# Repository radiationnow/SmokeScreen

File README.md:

# SmokeScreen
SmokeScreen is a NodeMCU/ESP32-based smoker temperature monitor/controller using MQTT for communication.

(Well, it'll be a controller some day.  For now, just a monitor.)

Simple circuit: NodeMCU ESP32 board, 2x 15k resistors to form the bottom leg of voltage dividers, and a pair of panel mount 2.5mm TS (mono) jacks.  (Fritzing only had stereo, but use mono.) 

Probe coefficients are hand calibrated using a known-good instant read thermometer, an ice bath, a warm bath, and a boiling bath.  Probes tested with include Thermoworks High Temp Air, Thermoworks normal probe, and a clone ET-733 probe.  Pit thermistor voltage divider center measured on pin 32, meat thermistor on pin 33.

Loosely inspired by CapnBry's HeaterMeter - https://github.com/CapnBry/HeaterMeter/.

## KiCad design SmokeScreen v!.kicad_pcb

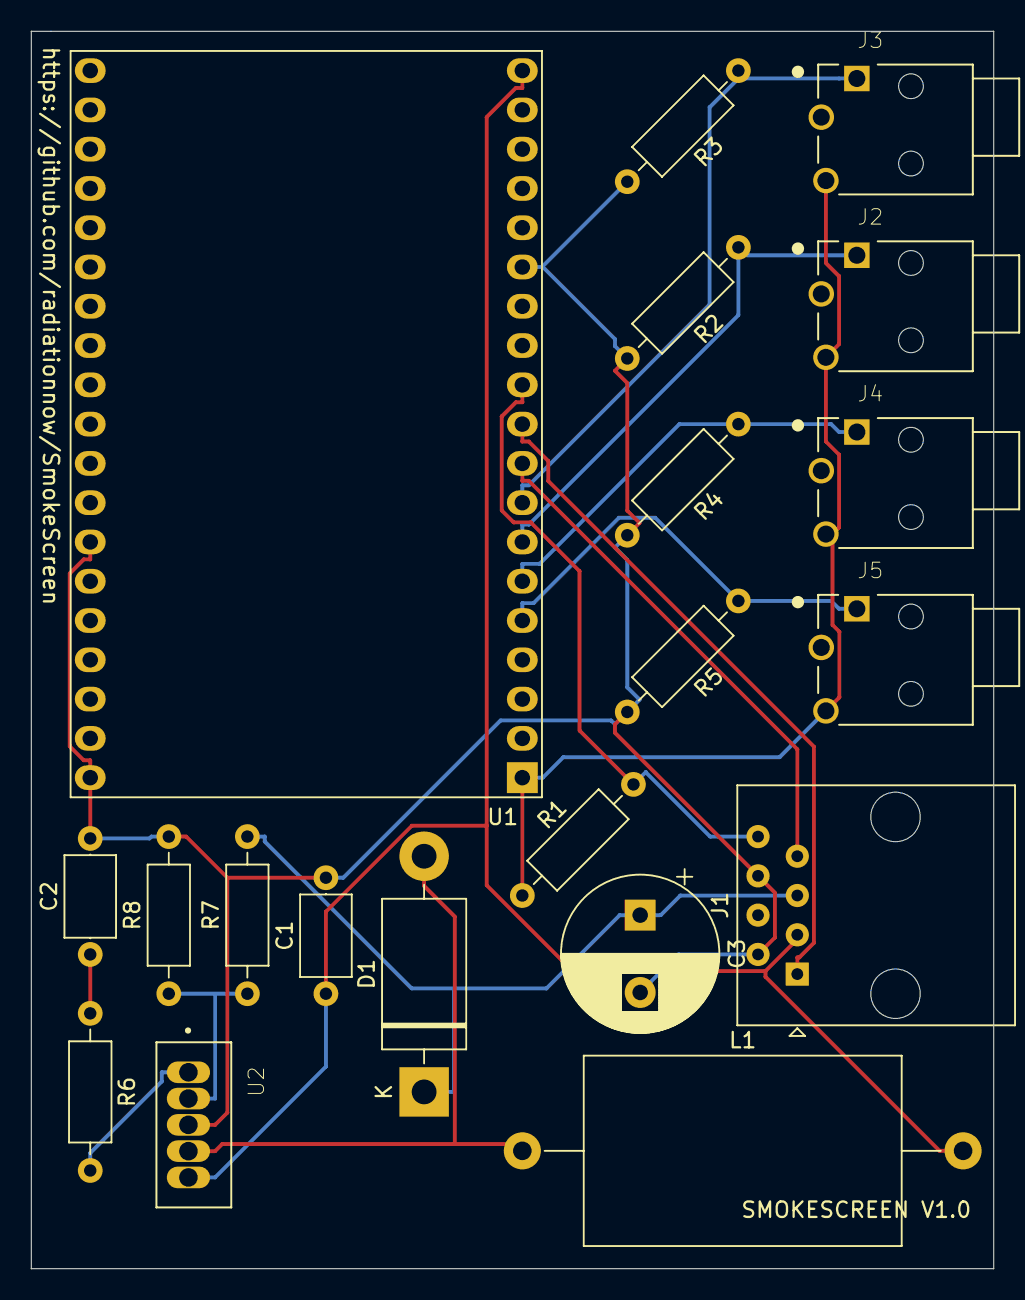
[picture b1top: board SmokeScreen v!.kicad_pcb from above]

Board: 2 copper layers, 62.2 x 80.0 mm, 20 parts (0 on the bottom side), 15 nets.

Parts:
C1: 0.1uF; C_Axial_L5.1mm_D3.1mm_P7.50mm_Horizontal
C2: .33uF; C_Axial_L5.1mm_D3.1mm_P7.50mm_Horizontal
C3: 680uF; CP_Radial_D10.0mm_P5.00mm
D1: 1N5821; D_DO-201AD_P15.24mm_Horizontal
J1: 8P8C; RJ45_Amphenol_54602-x08_Horizontal
J2, J3, J4, J5: MJ-2509N; CUI_MJ-2509N
L1: 100uH; L_Axial_L20.3mm_D12.1mm_P28.50mm_Horizontal_Vishay_IHA-101
R1: 4.7K; R_Axial_DIN0207_L6.3mm_D2.5mm_P10.16mm_Horizontal
R2, R3, R4, R5: 15K; R_Axial_DIN0207_L6.3mm_D2.5mm_P10.16mm_Horizontal
R6: 2.2K; R_Axial_DIN0207_L6.3mm_D2.5mm_P10.16mm_Horizontal
R7: 17.4K; R_Axial_DIN0207_L6.3mm_D2.5mm_P10.16mm_Horizontal
R8: 2K; R_Axial_DIN0207_L6.3mm_D2.5mm_P10.16mm_Horizontal
U1: NodeMCU_ESP-32S; NodeMCU-ESP32S
U2: LM2577T-12; VREG_LM2577T-12

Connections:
/FANPWM: J1.7, U1.9
/FAN_12V: C3.1, D1.1, J1.5, R7.2
/SERVO_PWM: J1.1, U1.10
/SERVO_VCC: C1.1, J1.3, L1.2, U1.19, U2.5
/TACH: J1.8, R1.2, U1.11
GND: C1.2, C2.2, C3.2, J1.2, J1.6, R2.2, R3.2, R4.2, R5.2, R8.2, U1.14, U1.32, U1.38, U2.3
unnamed: C2.1, R6.1
unnamed: D1.2, L1.1, U2.4
unnamed: J2.1, R2.1, U1.7
unnamed: J2.3, J3.3, J4.3, J5.3, R1.1, U1.1
unnamed: J3.1, R3.1, U1.8
unnamed: J4.1, R4.1, U1.6
unnamed: J5.1, R5.1, U1.5
unnamed: R6.2, U2.1
unnamed: R7.1, R8.1, U2.2

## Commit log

2019-12-23 Initial commit of NodeMCU code. (Monitor only, no controller, some controller-related MQTT stubs.)
2019-12-23 Readme update.
2020-05-06 Create LICENSE
2020-05-06 Schematic
2020-05-06 Add schematic image to readme.
2020-05-07 UNTESTED long-term plan schematic/PCB
    KiCad schematic and PCB file for a 4-channel version with PWMed blower and servo damper support over a single Ethernet cable. Uses a single 5V supply to drive everything, includes a 12V boost convert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
    THIS DESIGN IS UNTESTED AND SOFTWARE DOES NOT YET SUPPORT.
